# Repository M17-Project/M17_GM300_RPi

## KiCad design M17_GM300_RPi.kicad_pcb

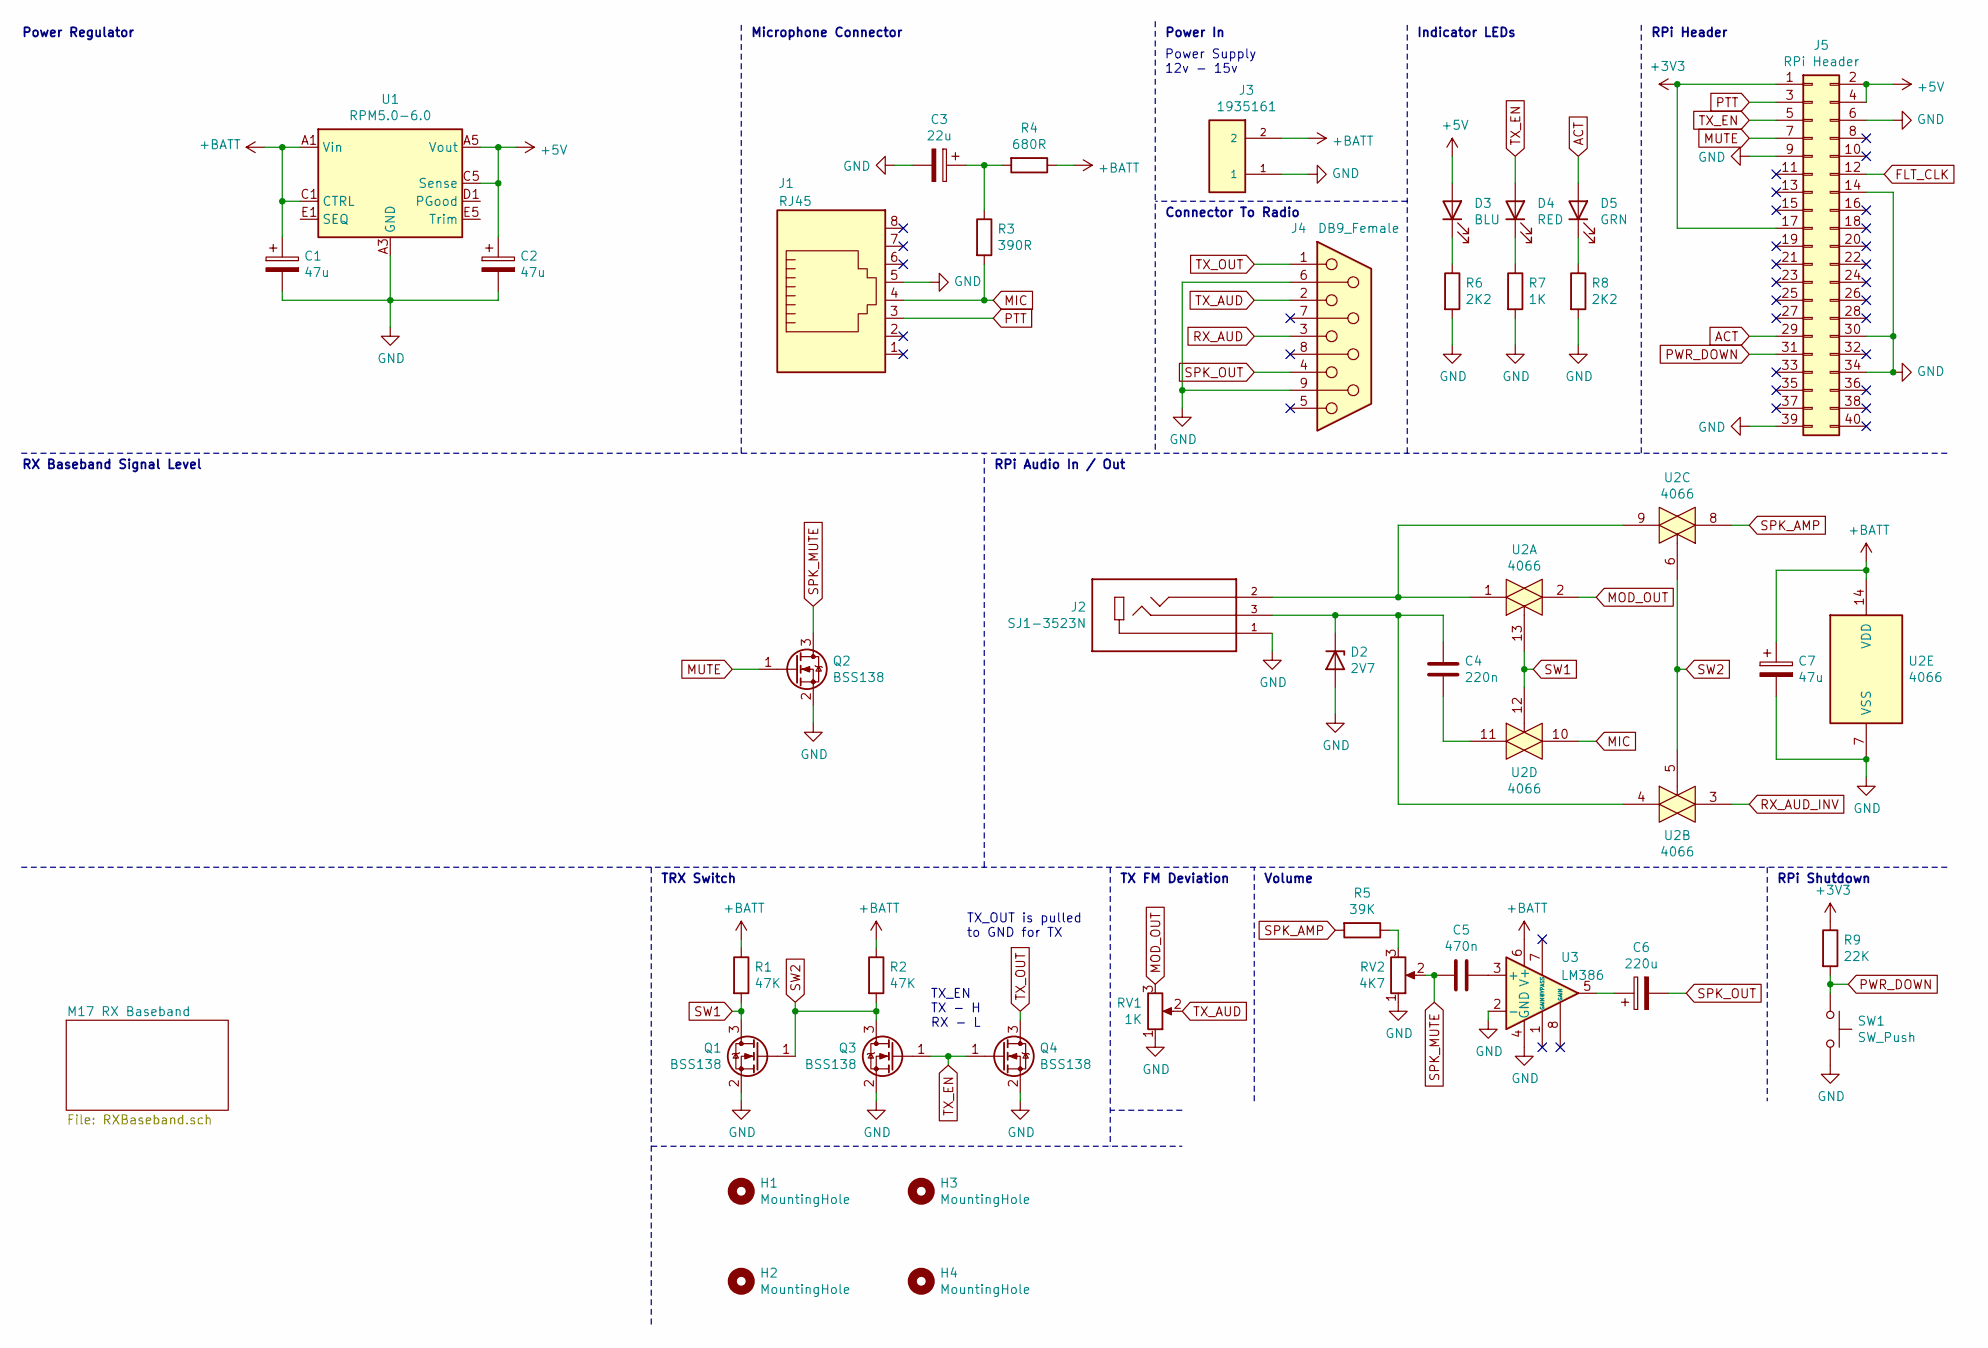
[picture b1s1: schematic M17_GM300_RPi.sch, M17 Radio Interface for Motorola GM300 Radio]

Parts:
C1, C2, C7: 47u; C_1206_3216Metric_Pad1.33x1.80mm_HandSolder
C3: 22u; C_0805_2012Metric_Pad1.18x1.45mm_HandSolder
C4: 220n; C_0805_2012Metric_Pad1.18x1.45mm_HandSolder
C5: 470n; C_0805_2012Metric_Pad1.18x1.45mm_HandSolder
C6: 220u; C_1206_3216Metric_Pad1.33x1.80mm_HandSolder
D2: 2V7; D_SOD-323F
D3: BLU; LED_0805_2012Metric_Pad1.15x1.40mm_HandSolder
D4: RED; LED_0805_2012Metric_Pad1.15x1.40mm_HandSolder
D5: GRN; LED_0805_2012Metric_Pad1.15x1.40mm_HandSolder
H1, H2, H3, H4: MountingHole; MountingHole_2.7mm_M2.5
J1: RJ45; RJ45_Amphenol_54602-x08_Horizontal
J2: SJ1-3523N; CUI_SJ1-3523N; PARTREV 1.02
J3: 1935161; PHOENIX_1935161
J4: DB9_Female; DSUB-9_Female_Horizontal_P2.77x2.84mm_EdgePinOffset4.94mm_H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
J5: RPi Header; PinSocket_2x20_P2.54mm_Vertical
Q1, Q2, Q3, Q4: BSS138; SOT-23
R1, R2: 47K; R_0805_2012Metric_Pad1.20x1.40mm_HandSolder
R3: 390R; R_0805_2012Metric_Pad1.20x1.40mm_HandSolder
R4: 680R; R_0805_2012Metric_Pad1.20x1.40mm_HandSolder
R5: 39K; R_0805_2012Metric_Pad1.20x1.40mm_HandSolder
R6, R8: 2K2; R_0805_2012Metric_Pad1.20x1.40mm_HandSolder
R7: 1K; R_0805_2012Metric_Pad1.20x1.40mm_HandSolder
R9: 22K; R_0805_2012Metric_Pad1.20x1.40mm_HandSolder
RV1: 1K; Potentiometer_Bourns_3361P_Vertical
RV2: 4K7; Potentiometer_Bourns_3361P_Vertical
SW1: SW_Push; SW_SPST_B3U-1000P
U1: RPM5.0-6.0
U2: 4066; SOIC-14_3.9x8.7mm_P1.27mm
U3: LM386; SOIC-8_3.9x4.9mm_P1.27mm

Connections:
+3V3: J5.1, J5.17, R9.1; also elsewhere on the board
+5V: C2.1, D3.2 (A), J5.2, J5.4, U1.A5 (Vout), U1.B5 (Vout), U1.C5 (Sense)
+BATT: C1.1, C7.1, J3.2, R1.1, R2.1, R4.1, U1.A1 (Vin), U1.A2 (Vin), U1.C1 (CTRL), U2.14 (VDD), U3.6 (V+)
ACT: D5.2 (A), J5.29
FLT_CLK: J5.12; also elsewhere on the board
GND: C1.2, C2.2, C3.2, C7.2, D2.2 (A), J1.5, J2.1, J3.1, J4.6, J4.9, J5.6, J5.9, J5.14, J5.30, J5.34, J5.39, Q1.2 (S), Q2.2 (S), Q3.2 (S), Q4.2 (S), R6.2, R7.2, R8.2, RV1.1, RV2.1, SW1.2, U1.A3 (GND), U1.A4 (GND), U1.B1 (GND), U1.B2 (GND), U1.B3 (GND), U1.B4 (GND), U1.C2 (GND), U1.C3 (GND), U1.C4 (GND), U1.D2 (GND), U1.D3 (GND), U1.D4 (GND), U1.D5 (GND), U1.E3 (GND), U1.E4 (GND), U2.7 (VSS), U3.2 (-), U3.4 (GND); also elsewhere on the board
MIC: J1.4, R3.2, U2.10
MOD_OUT: RV1.3, U2.2
MUTE: J5.7, Q2.1 (G)
unnamed: C3.1, R3.1, R4.2
unnamed: C4.1, D2.1 (K), J2.3, U2.4
unnamed: C4.2, U2.11
unnamed: C5.1, U3.3 (+)
unnamed: C6.1, U3.5
unnamed: D3.1 (K), R6.1
unnamed: D4.1 (K), R7.1
unnamed: D5.1 (K), R8.1
unnamed: J2.2, U2.1, U2.9
unnamed: R5.1, RV2.3
PTT: J1.3, J5.3
PWR_DOWN: J5.31, R9.2, SW1.1
RX_AUD: J4.3; also elsewhere on the board
RX_AUD_INV: U2.3; also elsewhere on the board
SPK_AMP: R5.2, U2.8
SPK_MUTE: C5.2, Q2.3 (D), RV2.2
SPK_OUT: C6.2, J4.4
SW1: Q1.3 (D), R1.2, U2.12, U2.13
SW2: Q1.1 (G), Q3.3 (D), R2.2, U2.5, U2.6
TX_AUD: J4.2, RV1.2
TX_EN: D4.2 (A), J5.5, Q3.1 (G), Q4.1 (G)
TX_OUT: J4.1, Q4.3 (D)

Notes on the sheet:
RPi Header
Indicator LEDs
Power In
Power Supply 12v - 15v
Connector To Radio
Microphone Connector
RPi Audio In / Out
RPi Shutdown
Volume
TX FM Deviation
TX_EN TX - H RX - L
TX_OUT is pulled to GND for TX
TRX Switch
Power Regulator
RX Baseband Signal Level

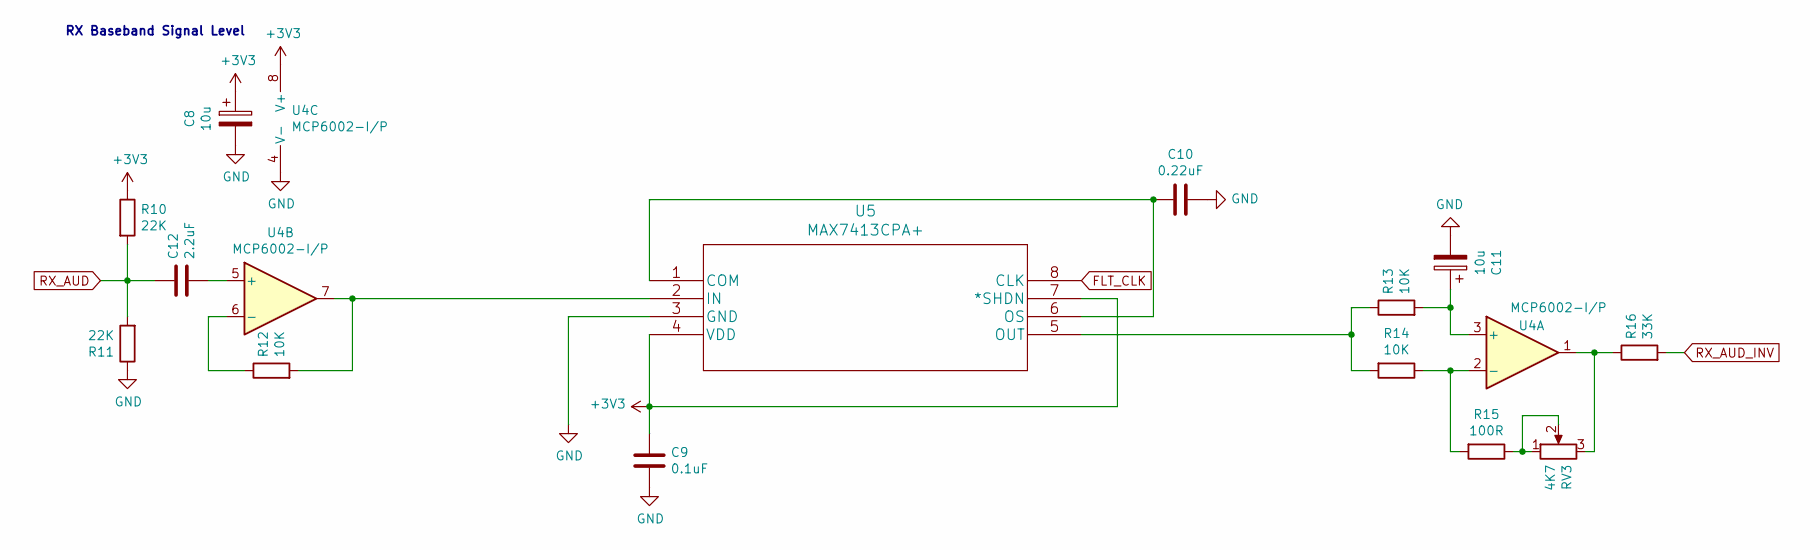
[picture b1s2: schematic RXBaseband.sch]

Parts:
C8, C11: 10u; C_0805_2012Metric_Pad1.18x1.45mm_HandSolder
C9: 0.1uF; C_0805_2012Metric_Pad1.18x1.45mm_HandSolder
C10: 0.22uF; C_0805_2012Metric_Pad1.18x1.45mm_HandSolder
C12: 2.2uF; C_0805_2012Metric_Pad1.18x1.45mm_HandSolder
R10, R11: 22K; R_0805_2012Metric_Pad1.20x1.40mm_HandSolder
R12, R13, R14: 10K; R_0805_2012Metric_Pad1.20x1.40mm_HandSolder
R15: 100R; R_0805_2012Metric_Pad1.20x1.40mm_HandSolder
R16: 33K; R_0805_2012Metric_Pad1.20x1.40mm_HandSolder
RV3: 4K7; Potentiometer_Bourns_3361P_Vertical
U4: MCP6002-I/P; MSOP-8_3x3mm_P0.65mm
U5: MAX7413CPA+; MSOP-8_3x3mm_P0.65mm

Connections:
+3V3: C8.1, C9.1, R10.1, U4.8 (V+), U5.4 (VDD), U5.7 (*SHDN); also elsewhere on the board
FLT_CLK: U5.8 (CLK); also elsewhere on the board
GND: C8.2, C9.2, C10.1, C11.2, R11.1, U4.4 (V-), U5.3 (GND); also elsewhere on the board
unnamed: C10.2, U5.1 (COM), U5.6 (OS)
unnamed: C11.1, R13.2, U4.3 (+)
unnamed: C12.2, U4.5 (+)
unnamed: R12.1, U4.6 (-)
unnamed: R12.2, U4.7, U5.2 (IN)
unnamed: R13.1, R14.2, U5.5 (OUT)
unnamed: R14.1, R15.2, U4.2 (-)
unnamed: R15.1, RV3.1, RV3.2
unnamed: R16.1, RV3.3, U4.1
RX_AUD: C12.1, R10.2, R11.2; also elsewhere on the board
RX_AUD_INV: R16.2; also elsewhere on the board

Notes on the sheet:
RX Baseband Signal Level

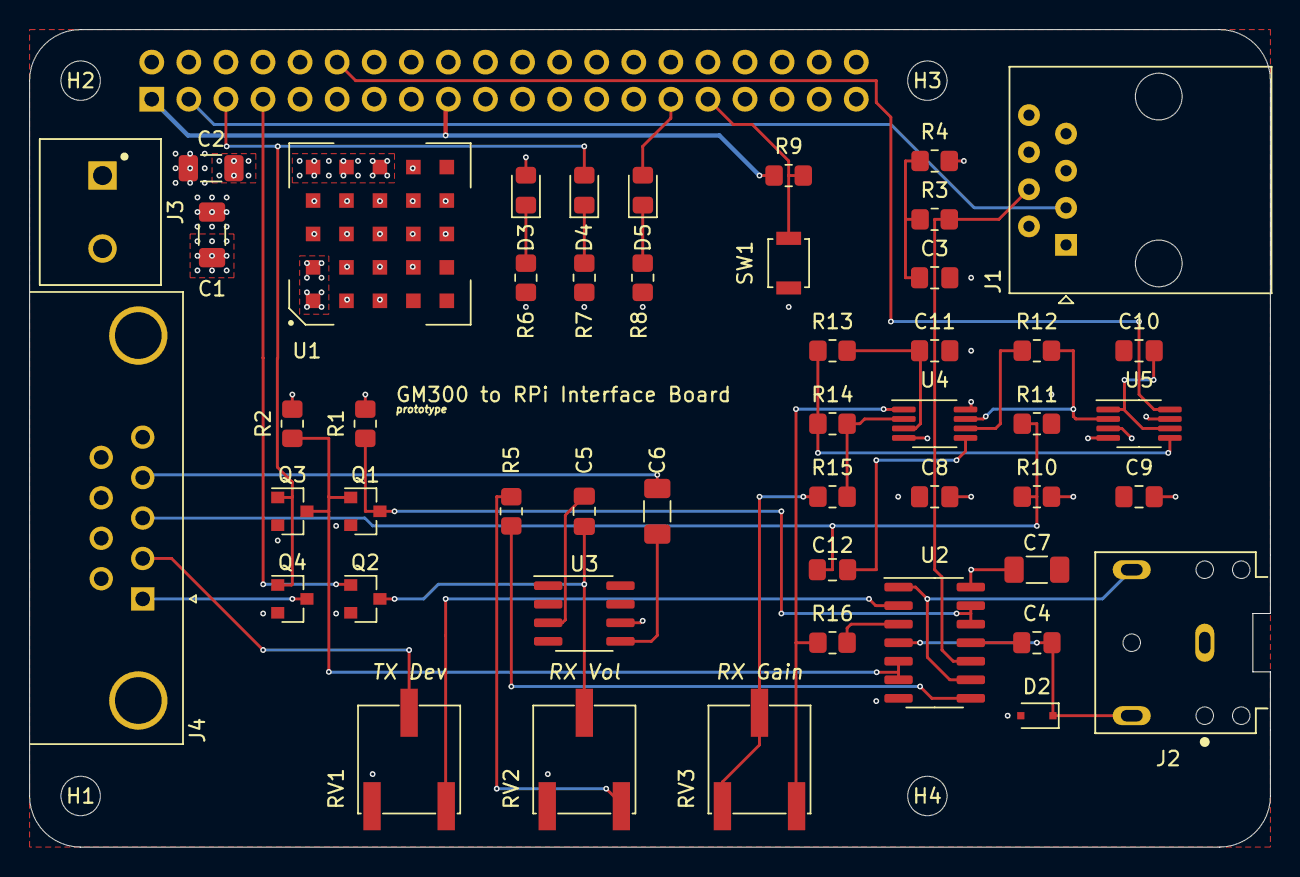
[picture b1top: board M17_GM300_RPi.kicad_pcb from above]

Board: 4 copper layers, 85.0 x 56.0 mm, 54 parts (1 on the bottom side), 40 nets.

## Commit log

2021-02-25 change board to radio connector
2021-02-25 clean up a few erc warnings
2021-02-25 fixin' labels
2021-02-25 pushin' pushin' pushin'
2021-02-25 add pdf
2021-02-25 some changes, bro. new pdf
2021-02-25 sync
2021-02-25 redraw
2021-02-25 remove unused
2021-02-25 update in-progress pdf
2021-02-26 little things
2021-02-26 draft alpha
2021-03-16 add part
2021-03-17 it aint pretty.
2021-03-18 smps
2021-04-03 change footprints to smd where aplicable
2021-04-03 initial pcb layout, change smds to 0603
2021-04-03 pcb parts grouped by function
2021-04-05 Created new symbol and footprint for new power supply; removed old and added new power supply to schem; updated pcb with the changes.
2021-04-08 increased passives to 0805. preliminary layout.
2021-04-10 updated layout to proposed final
2021-04-10 missed file
2021-04-23 part and footprint updates, routing
    updated parts and footprints for header and transistors. updated layout. most routing is complete pending changes to schematic.
2021-04-28 ibom draft
2021-04-28 push D5 up a bit, add models
2021-04-28 put pin 17 on 3v3
2021-04-28 updated 3v3 power trace, led alignments
2021-04-28 change c1 c2, update bom
2021-04-28 change c7, update bom
2021-04-28 updated routing and labeling for c7
